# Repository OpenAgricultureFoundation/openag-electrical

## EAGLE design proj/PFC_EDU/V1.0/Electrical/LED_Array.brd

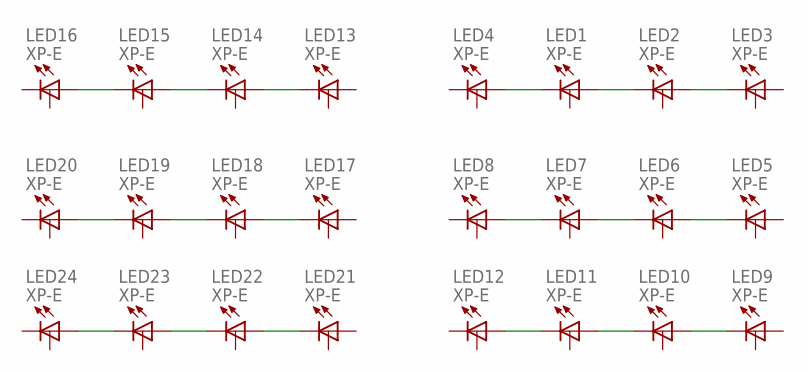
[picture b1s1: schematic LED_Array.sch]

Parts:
LED1, LED2, LED3, LED4, LED5, LED6, LED7, LED8, LED9, LED10, LED11, LED12, LED13, LED14, LED15, LED16, LED17, LED18, LED19, LED20, LED21, LED22, LED23, LED24: XP-E; CREE-XLAMP-XP-E

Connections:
unnamed: LED1.C, LED1.C@1 (C), LED4.A, LED4.A@1 (A)
unnamed: LED1.A, LED1.A@1 (A), LED2.C, LED2.C@1 (C)
unnamed: LED2.A, LED2.A@1 (A), LED3.C, LED3.C@1 (C)
unnamed: LED7.C, LED7.C@1 (C), LED8.A, LED8.A@1 (A)
unnamed: LED6.C, LED6.C@1 (C), LED7.A, LED7.A@1 (A)
unnamed: LED5.C, LED5.C@1 (C), LED6.A, LED6.A@1 (A)
unnamed: LED11.C, LED11.C@1 (C), LED12.A, LED12.A@1 (A)
unnamed: LED10.C, LED10.C@1 (C), LED11.A, LED11.A@1 (A)
unnamed: LED9.C, LED9.C@1 (C), LED10.A, LED10.A@1 (A)
unnamed: LED15.C, LED15.C@1 (C), LED16.A, LED16.A@1 (A)
unnamed: LED14.C, LED14.C@1 (C), LED15.A, LED15.A@1 (A)
unnamed: LED13.C, LED13.C@1 (C), LED14.A, LED14.A@1 (A)
unnamed: LED19.C, LED19.C@1 (C), LED20.A, LED20.A@1 (A)
unnamed: LED18.C, LED18.C@1 (C), LED19.A, LED19.A@1 (A)
unnamed: LED17.C, LED17.C@1 (C), LED18.A, LED18.A@1 (A)
unnamed: LED23.C, LED23.C@1 (C), LED24.A, LED24.A@1 (A)
unnamed: LED22.C, LED22.C@1 (C), LED23.A, LED23.A@1 (A)
unnamed: LED21.C, LED21.C@1 (C), LED22.A, LED22.A@1 (A)

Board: 2 copper layers, 24 parts (0 on the bottom side), 18 nets, no tracks yet.

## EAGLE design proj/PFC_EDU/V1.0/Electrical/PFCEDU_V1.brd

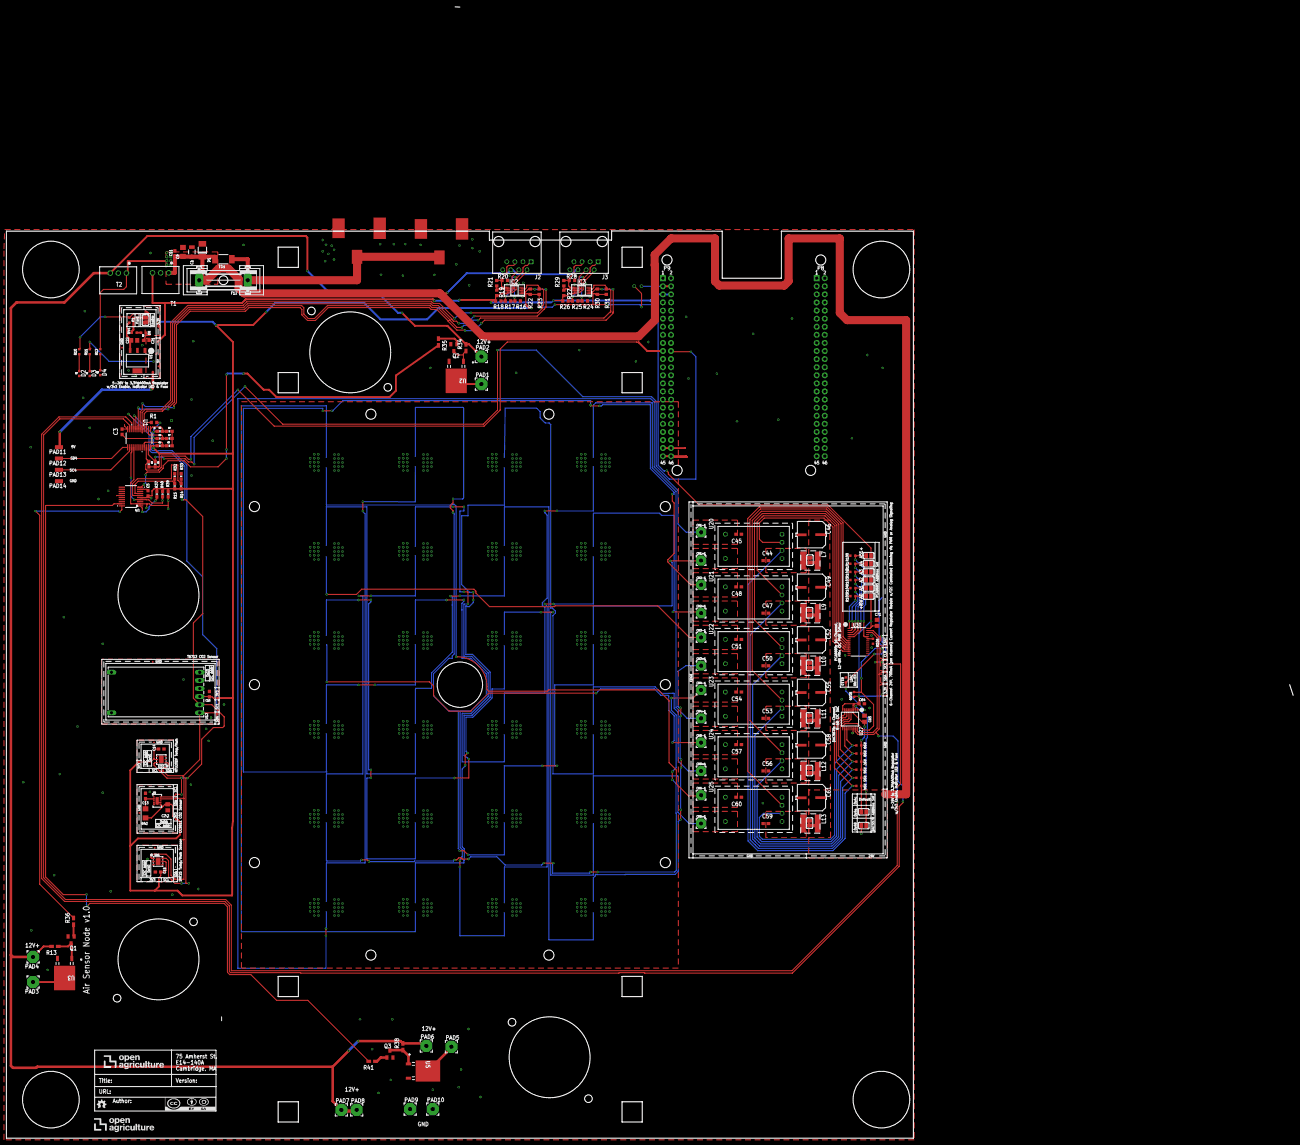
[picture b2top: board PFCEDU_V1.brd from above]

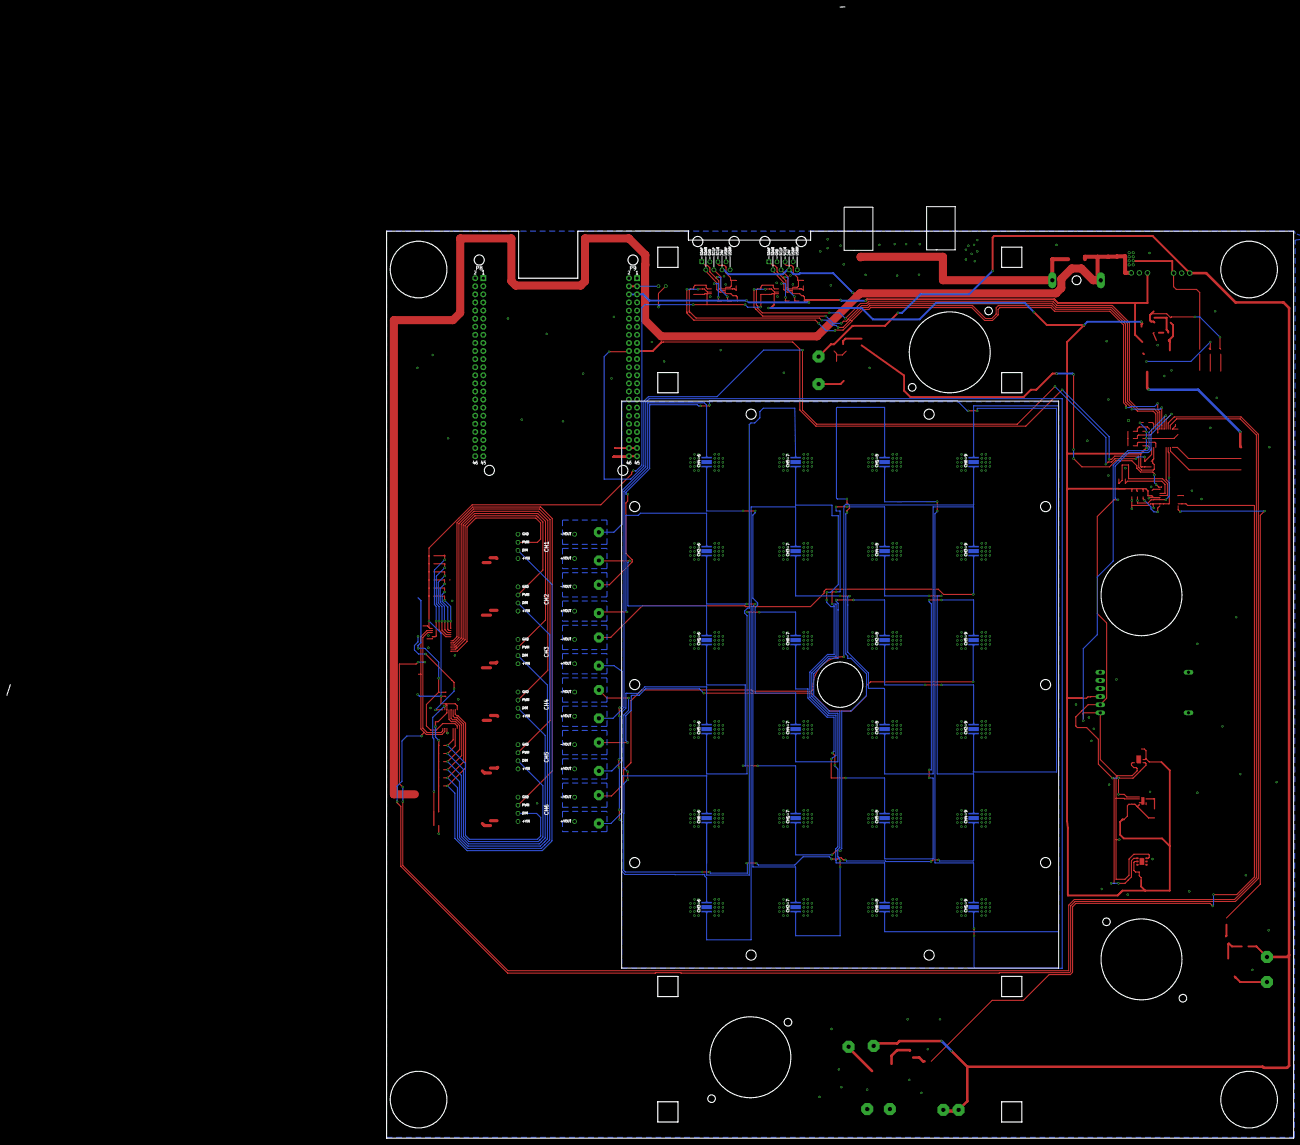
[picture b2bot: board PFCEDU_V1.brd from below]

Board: 2 copper layers, 284.7 x 284.8 mm, 221 parts (24 on the bottom side), 114 nets.

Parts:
ATTRIBUTES: DOCFIELD
C1: 4.7uF; CAP_C1206
C2\2, C65: 4.7uF; C0805
C3, C5, C11: .1uF; C0603@1
C9: 10uF; C1206
C13, C14, C15, C16, C21, C64: 0.1uF; C0603
C22, C71: 10uF; C0805
C44, C45, C47, C48, C50, C51, C53, C54, C56, C57, C59, C60: 10nF; C0603
C46, C49, C52, C55, C58, C61: 100uF; EEE-1HA101UP
CH1+1, CH1-1, CH2+1, CH2-1, CH3+1, CH3-1, CH4+1, CH4-1, CH5+1, CH5-1, CH6+1, CH6-1: 3,17/1,3
CH1-6, CH1-7, CH1-8, CH1-9, CH2-6, CH2-7, CH2-8, CH2-9, CH3-6, CH3-7, CH3-8, CH3-9, CH4-6, CH4-7, CH4-8, CH4-9, CH5-6, CH5-7, CH5-8, CH5-9, CH6-6, CH6-7, CH6-8, CH6-9: XP-E; CREE-XLAMP-XP-E
D1: SMAJ14A; DO-214AC
D2, D3, D4, D8: APT1608CGCK; CHIPLED_0603
F1: 0448.400MR; 0603
F11: SST 7; SS
F12: GSH15
IC2, IC3: PCA9615DP; SOP50P490X110-10N
J2, J3: 54602-908LF; OPENAG-V1-RJ45
L7, L9, L10, L11, L12, L13: 120uH; 74404064121
PAD1, PAD2, PAD3, PAD4, PAD5, PAD6, PAD7, PAD8, PAD9, PAD10: WIREPAD3,81/1,3; 3,81/1,3
PAD11, PAD12, PAD13, PAD14: SMD1,27-2,54
Q1, Q2, Q3: MMBT2222A; SOT23-BEC
R1, R22, R23, R30, R31: 10K; R0603
R2, R3, R4, R5, R6, R7, R8, R9, R14, R15, R32, R33, R37, R39, R40: 10K; 0603-RES
R10, R11, R12, R44: 100; RC0603N
R13, R34, R35, R36, R38, R41: R0805W
R16, R18, R19, R20, R24, R26, R27, R28: 600; R0603
R17, R21, R25, R29: 120; R0603
R42: 4.7K; R1206
R94, R95, R96, R97, R98, R99, R109: 1K; RC0603N
R100, R101, R102, R103, R104, R105, R106: 10K; RC0603N
R110: 0 OHM; RC0603N
SJ1: SOLDERJUMPER_REFLOW_NOPASTE
SJ_A18, SJ_A19, SJ_A20, SJ_A21, SJ_A22, SJ_A23, SJ_A24, SJ_A25, SJ_A26, SJ_A27, SJ_A28, SJ_A29, SJ_A34, SJ_A35: SOLDERJUMPER_REFLOW_NOPASTE
T1: R-78E5.0-1.0
T2: R-78E12.0-1.0; R-78E5.0-1.0
TP1, TP2, TP3, TP5, TP6, TP7, TP36, TP37, TP38, TP39, TP40, TP41, TP42, TP43, TP44, TP45, TP61, TP62, TP63: TPTP06R; TP06R
U1: TCA9548APWRPW24-M; PW24-M
U2, U3, U5: STD12NF06LT4; DPAK
U4: PCF8574APWRPW20-M; PW20-M
U9: CCS811
U10: HPP845E034R5; HTU20D(F)
U11: SHT25; SHT2X
U12: T6713-5K; T6713
U17: LM2937IMP3.3NOPB; MP04A
U20, U21, U22, U23, U24, U25: RCD-24-0.70/VREF; RCD-24-PINNED
U27: DAC5578SPW; TSSOP16
U30: PCA9685; TSSOP28
U$1, U$3: PJ-036AH
U$2: BEAGLE_BONE_BLACK_CAPE
U$9: OPENAG-LOGO-750-MIL

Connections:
24V_IN: F11.1, F12.1, U$1.1, U$3.1
!LDAC!: R110.2, U27.1
+3V3: C2\2.1, C3.1, C5.1, C14.1, C15.1, C16.1, C64.1, C65.1, C71.1, F1.2, IC2.1, IC3.1, R1.2, R2.2, R4.2, R6.2, R8.2, R9.2, R10.2, R14.2, R15.2, R22.2, R23.2, R30.2, R31.2, R37.2, R39.2, R40.2, R42.2, R94.1, R95.1, R96.1, R97.1, R98.1, R99.1, R109.1, SJ1.2, SJ_A18.1, SJ_A19.1, SJ_A20.1, SJ_A21.1, SJ_A22.1, SJ_A23.1, SJ_A34.1, TP5.TP, TP36.TP, TP41.TP, TP44.TP, TP63.TP, U1.24, U4.5, U9.6, U10.5, U11.5, U12.3, U27.3, U27.8, U30.28, U$2.P9.3, U$2.P9.4
+5V: C21.1, IC2.10, IC3.10, PAD11.1, R11.2, R18.1, R19.2, R26.1, R27.2, T1.3, TP62.TP, U17.1, U$2.P9.5, U$2.P9.6
+12V: PAD2.1, PAD4.1, PAD6.1, PAD7.1, PAD8.1, R13.2, R34.2, R38.2, T2.3
+24V: C1.1, C9.1, C11.1, C46.+, C49.+, C52.+, C55.+, C58.+, C61.+, D1.C, F11.2, F12.2, J2.24V(6), J3.24V(6), L7.1, L9.1, L10.1, L11.1, L12.1, L13.1, R12.2, SJ_A24.2, SJ_A25.2, SJ_A26.2, SJ_A27.2, SJ_A28.2, SJ_A29.2, T1.1, T2.1
A0: R105.2, SJ_A18.2, U30.1
A0_EXT_1: R4.1, R5.2, U1.1
A0_IO: R14.1, R33.2, U4.6
A1: R104.2, SJ_A19.2, U30.2
A1_EXT_1: R6.1, R7.2, U1.2
A1_IO: R15.1, R32.2, U4.7
A2: R103.2, SJ_A20.2, U30.3
A2_EXT_1: R2.1, R3.2, U1.21
A3: R102.2, SJ_A21.2, U30.4
A4: R101.2, SJ_A22.2, U30.5
A5: R100.2, SJ_A23.2, U30.24
ADDR0: SJ_A34.2, SJ_A35.2, U27.2
CH1+: CH1+1.1, CH1-6.A, CH1-6.A@1, U20.6
CH1-: C45.1, CH1-1.1, CH1-9.C, CH1-9.C@1, U20.5
CH2+: CH2+1.1, CH2-6.A, CH2-6.A@1, U21.6
CH2-: C48.1, CH2-1.1, CH2-9.C, CH2-9.C@1, U21.5
CH3+: CH3+1.1, CH3-6.A, CH3-6.A@1, U22.6
CH3-: C51.1, CH3-1.1, CH3-9.C, CH3-9.C@1, U22.5
CH4+: CH4+1.1, CH4-6.A, CH4-6.A@1, U23.6
CH4-: C54.1, CH4-1.1, CH4-9.C, CH4-9.C@1, U23.5
CH5+: CH5+1.1, CH5-6.A, CH5-6.A@1, U24.6
CH5-: C57.1, CH5-1.1, CH5-9.C, CH5-9.C@1, U24.5
CH6+: CH6+1.1, CH6-6.A, CH6-6.A@1, U25.6
CH6-: C60.1, CH6-1.1, CH6-9.C, CH6-9.C@1, U25.5
DAC_!CLR!: R109.2, U27.9
DIM1: R94.2, U20.2, U27.7
DIM2: R95.2, U21.2, U27.6
DIM3: R96.2, U22.2, U27.5
DIM4: R97.2, U23.2, U27.4
DIM5: R98.2, U24.2, U27.10
DIM6: R99.2, U25.2, U27.11
DSCLM0: IC2.6, J2.DSCLM(5), R20.2, R21.1
DSCLM1: IC3.6, J3.DSCLM(5), R28.2, R29.1
DSCLP0: IC2.7, J2.DSCLP(4), R19.1, R21.2
DSCLP1: IC3.7, J3.DSCLP(4), R27.1, R29.2
DSDAM0: IC2.9, J2.DSDAM(2), R16.1, R17.2
DSDAM1: IC3.9, J3.DSDAM(2), R24.1, R25.2
DSDAP0: IC2.8, J2.DSDAP(1), R17.1, R18.2
DSDAP1: IC3.8, J3.DSDAP(1), R25.1, R26.2
GND: C1.2, C2\2.2, C3.2, C5.2, C9.2, C11.2, C13.2, C14.2, C15.2, C16.2, C21.2, C22.2, C44.2, C45.2, C46.-, C47.2, C48.2, C49.-, C50.2, C51.2, C52.-, C53.2, C54.2, C55.-, C56.2, C57.2, C58.-, C59.2, C60.2, C61.-, C64.2, C65.2, C71.2, D1.A, D2.C, D3.C, D4.C, D8.C, IC2.5, IC3.5, J2.GND(3), J3.GND(3), PAD9.1, PAD10.1, PAD14.1, Q1.E, Q2.E, Q3.E, R3.1, R5.1, R7.1, R16.2, R20.1, R24.2, R28.1, R32.1, R33.1, R100.1, R101.1, R102.1, R103.1, R104.1, R105.1, R106.2, R110.1, SJ_A35.1, T1.2, T2.2, TP3.TP, TP37.TP, TP40.TP, TP45.TP, TP61.TP, U1.12, U2.2, U3.2, U4.9, U4.15, U5.2, U9.1, U9.7, U9.EP, U10.2, U11.2, U12.4, U12.6, U17.2, U17.4, U20.4, U21.4, U22.4, U23.4, U24.4, U25.4, U27.14, U30.14, U30.25, U$1.2, U$1.3, U$2.P8.1, U$2.P8.2, U$2.P9.1, U$2.P9.2, U$2.P9.43, U$2.P9.44, U$2.P9.45, U$2.P9.46, U$3.2, U$3.3
MOS1: PAD3.1, U3.3
MOS2: PAD1.1, U2.3
MOS3: PAD5.1, U5.3
unnamed: D3.A, R11.1
unnamed: D4.A, R12.1
unnamed: Q1.C, R13.1, U3.1
unnamed: Q1.B, R36.1
unnamed: D2.A, R10.1
unnamed: R37.1, U4.1
unnamed: Q2.C, R34.1, U2.1
unnamed: Q2.B, R35.1
unnamed: Q3.C, R38.1, U5.1
unnamed: Q3.B, R41.1
unnamed: CH2-8.C, CH2-8.C@1, CH2-9.A, CH2-9.A@1
unnamed: CH2-7.C, CH2-7.C@1, CH2-8.A, CH2-8.A@1
unnamed: CH2-6.C, CH2-6.C@1, CH2-7.A, CH2-7.A@1
unnamed: CH4-8.C, CH4-8.C@1, CH4-9.A, CH4-9.A@1
unnamed: CH4-7.C, CH4-7.C@1, CH4-8.A, CH4-8.A@1
unnamed: CH4-6.C, CH4-6.C@1, CH4-7.A, CH4-7.A@1
unnamed: CH6-8.C, CH6-8.C@1, CH6-9.A, CH6-9.A@1
unnamed: CH6-7.C, CH6-7.C@1, CH6-8.A, CH6-8.A@1
unnamed: C44.1, L7.2, SJ_A24.1, U20.1
unnamed: C47.1, L9.2, SJ_A25.1, U21.1
unnamed: C50.1, L10.2, SJ_A26.1, U22.1
unnamed: C53.1, L11.2, SJ_A27.1, U23.1
unnamed: U9.4, U9.5
unnamed: C13.1, R42.1, U9.2
unnamed: C56.1, L12.2, SJ_A28.1, U24.1
unnamed: C59.1, L13.2, SJ_A29.1, U25.1
unnamed: CH6-6.C, CH6-6.C@1, CH6-7.A, CH6-7.A@1
unnamed: CH1-8.C, CH1-8.C@1, CH1-9.A, CH1-9.A@1
unnamed: CH1-7.C, CH1-7.C@1, CH1-8.A, CH1-8.A@1
unnamed: CH1-6.C, CH1-6.C@1, CH1-7.A, CH1-7.A@1
unnamed: CH3-8.C, CH3-8.C@1, CH3-9.A, CH3-9.A@1
unnamed: CH3-7.C, CH3-7.C@1, CH3-8.A, CH3-8.A@1
unnamed: CH3-6.C, CH3-6.C@1, CH3-7.A, CH3-7.A@1
unnamed: CH5-8.C, CH5-8.C@1, CH5-9.A, CH5-9.A@1
unnamed: CH5-7.C, CH5-7.C@1, CH5-8.A, CH5-8.A@1
unnamed: CH5-6.C, CH5-6.C@1, CH5-7.A, CH5-7.A@1
unnamed: D8.A, R44.1
unnamed: C22.1, F1.1, U17.3
OE: R106.1, U30.23
P0_IO: R35.2, U4.10
P6_IO: R41.2, U4.19
P7_IO: R36.2, U4.20
PWM1: U20.3, U30.12
PWM2: U21.3, U30.11
PWM3: U22.3, U30.10
PWM4: U23.3, U30.9
PWM5: U24.3, U30.8
PWM6: U25.3, U30.7
REG_3V3_400MA: R44.2, SJ1.1
RESET1: R1.1, U1.3
SC0: IC2.4, R23.1, U1.5
SC1: IC3.4, R31.1, U1.7
SC2: TP1.TP, TP7.TP, TP39.TP, TP43.TP, U1.9, U9.10, U10.6, U11.6, U12.2
SC3: U1.11, U27.16, U30.26
SC4: PAD13.1, U1.14
SC5: R39.1, U1.16, U4.2
SCL: R8.1, U1.22, U$2.P9.19
SD0: IC2.2, R22.1, U1.4
SD1: IC3.2, R30.1, U1.6
SD2: TP2.TP, TP6.TP, TP38.TP, TP42.TP, U1.8, U9.9, U10.1, U11.1, U12.1
SD3: U1.10, U27.15, U30.27
SD4: PAD12.1, U1.13
SD5: R40.1, U1.15, U4.4
SDA: R9.1, U1.23, U$2.P9.20
T1: CH1-6.THERM, CH1-7.THERM, CH1-8.THERM, CH1-9.THERM, CH2-6.THERM, CH2-7.THERM, CH2-8.THERM, CH2-9.THERM, CH3-6.THERM, CH3-7.THERM, CH3-8.THERM, CH3-9.THERM, CH4-6.THERM, CH4-7.THERM, CH4-8.THERM, CH4-9.THERM, CH5-6.THERM, CH5-7.THERM, CH5-8.THERM, CH5-9.THERM, CH6-6.THERM, CH6-7.THERM, CH6-8.THERM, CH6-9.THERM

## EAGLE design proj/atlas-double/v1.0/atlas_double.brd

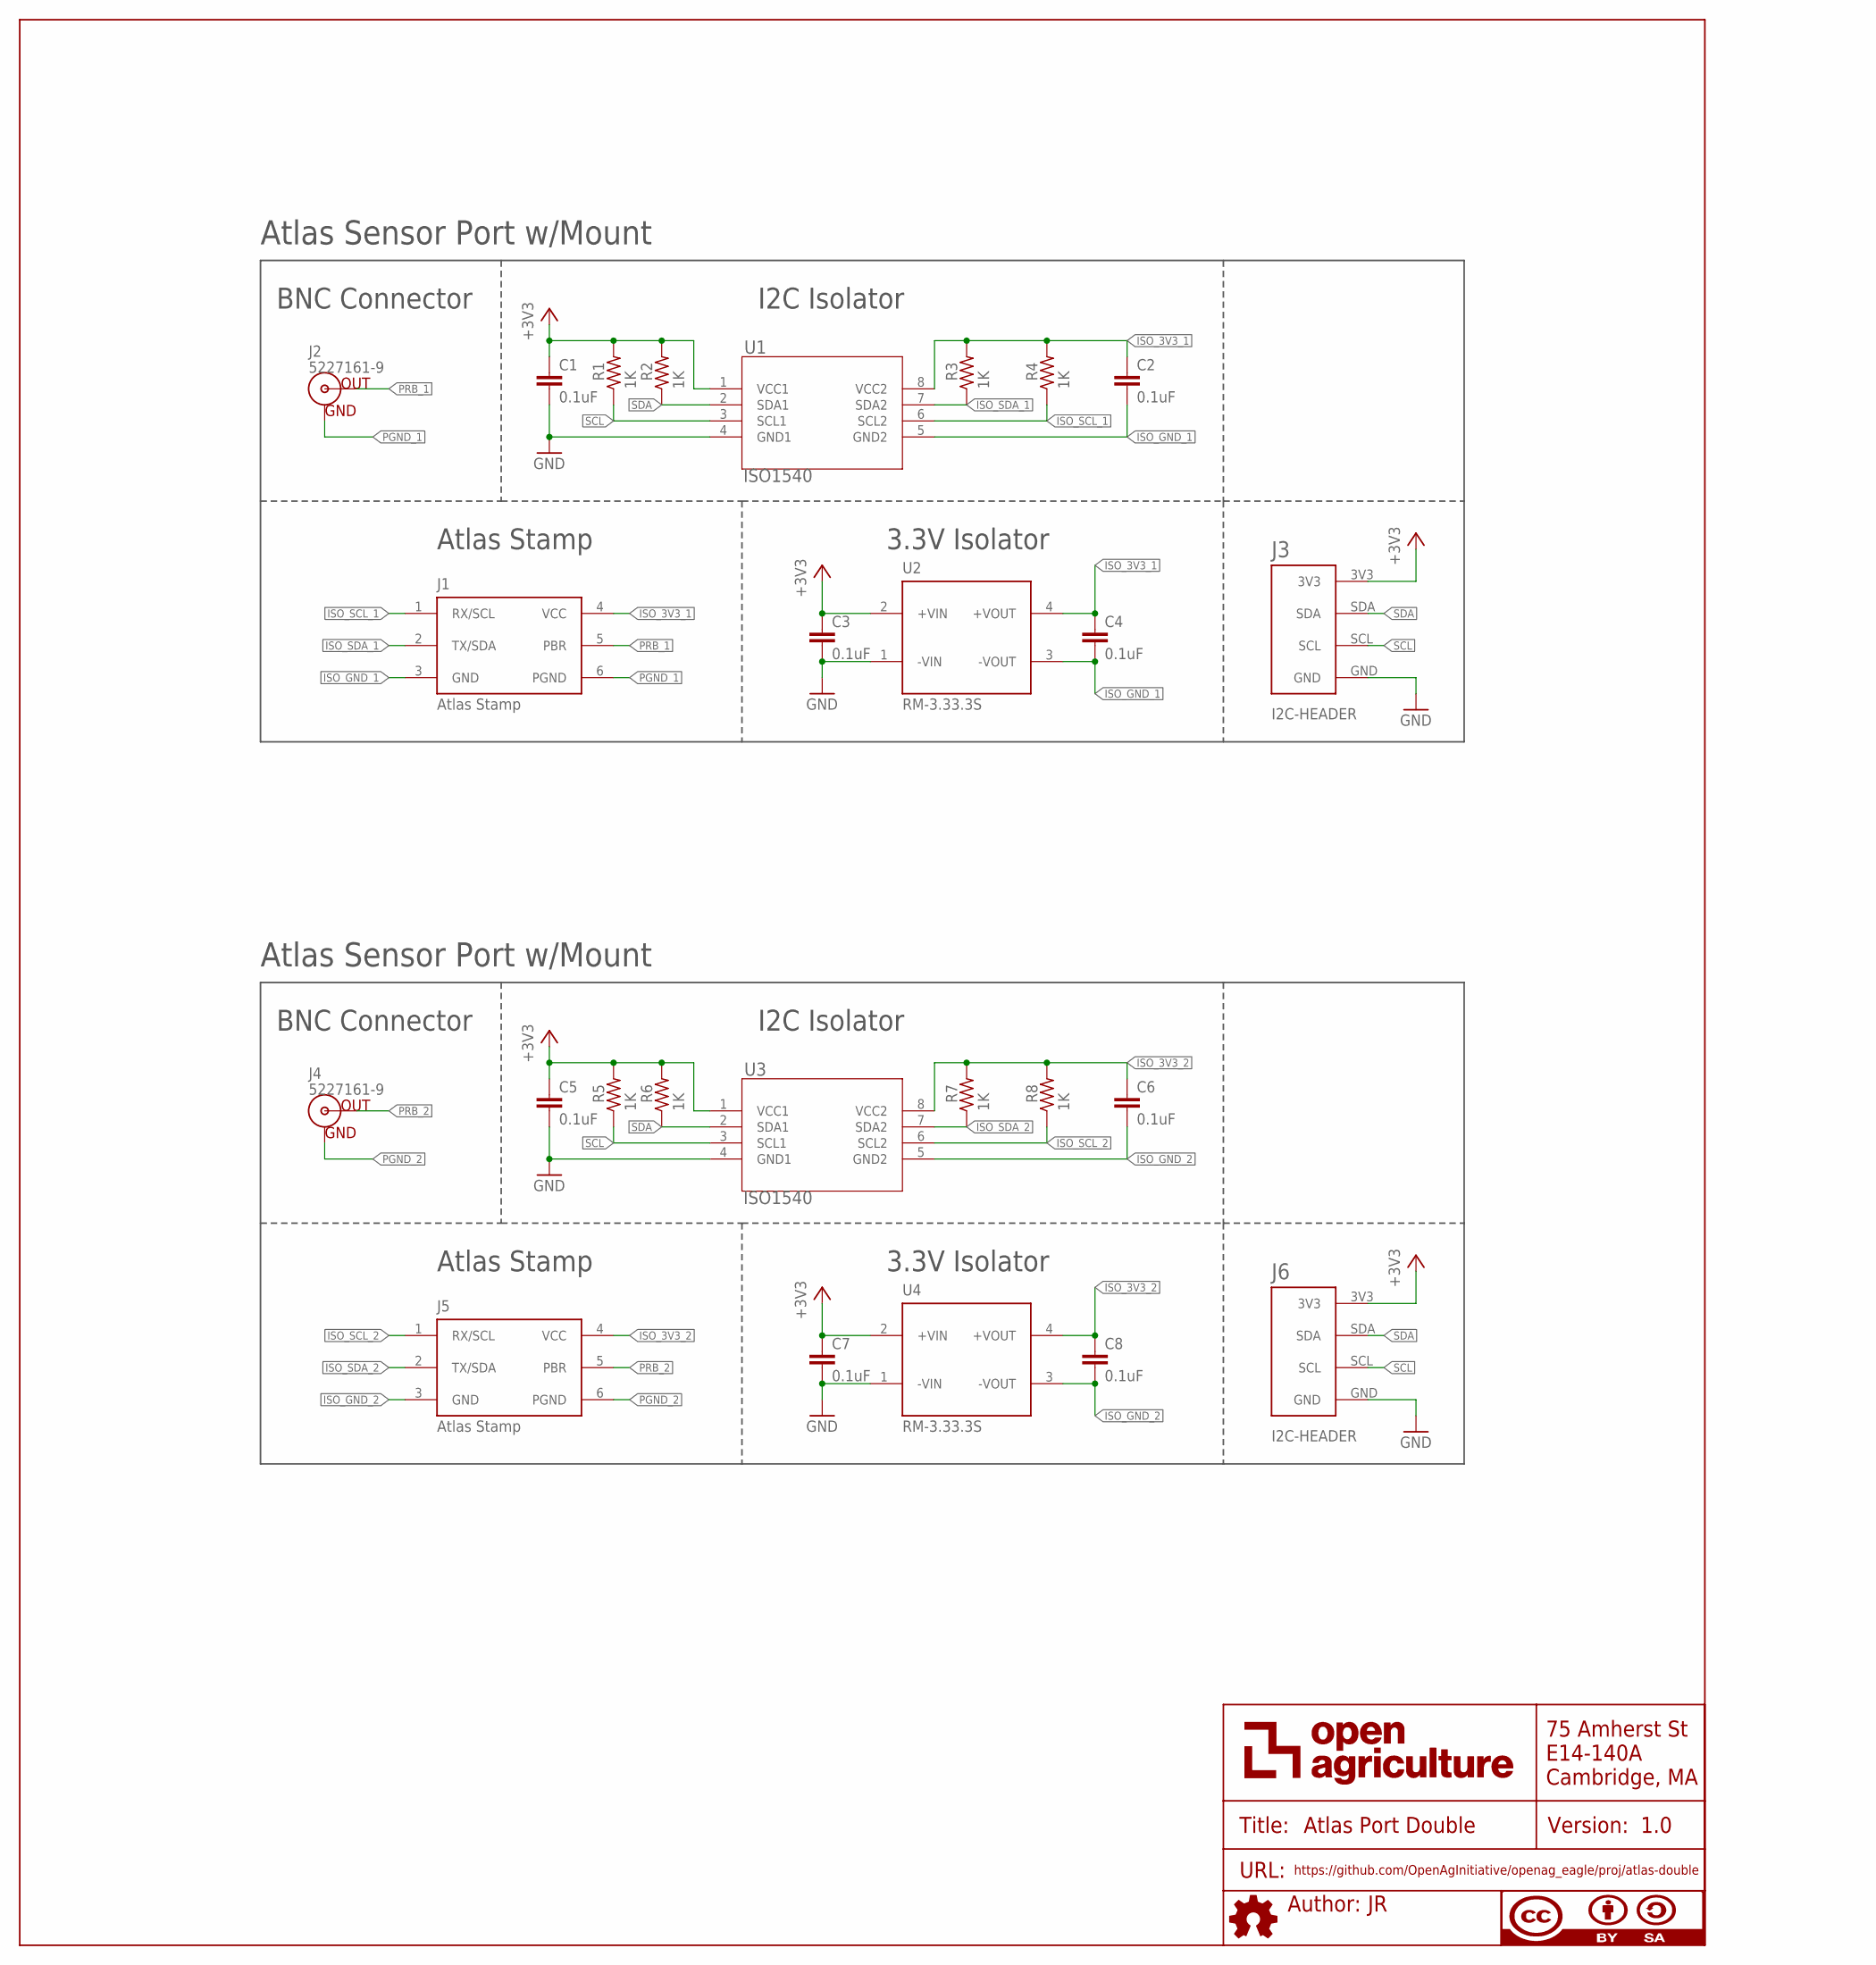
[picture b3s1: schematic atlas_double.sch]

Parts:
C1, C2, C3, C4, C5, C6, C7, C8: 0.1uF; C0603
FRAME1: DOCFIELD
J1, J5: Atlas Stamp; ATLAS-STAMP
J2, J4: 5227161-9; BNC
J3, J6: I2C-HEADER; OPENAG-I2C-HEADER
R1, R2, R3, R4, R5, R6, R7, R8: 1K; RC0603N
U1, U3: ISO1540; D8
U2, U4: RM-3.33.3S; SIP4

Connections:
+3V3: C1.1, C3.1, C5.1, C7.1, J3.3V3, J6.3V3, R1.2, R2.2, R5.2, R6.2, U1.1 (VCC1), U2.2 (+VIN), U3.1 (VCC1), U4.2 (+VIN)
GND: C1.2, C3.2, C5.2, C7.2, J3.GND, J6.GND, U1.4 (GND1), U2.1 (-VIN), U3.4 (GND1), U4.1 (-VIN)
ISO_3V3_1: C2.1, C4.1, J1.4 (VCC), R3.2, R4.2, U1.8 (VCC2), U2.4 (+VOUT)
ISO_3V3_2: C6.1, C8.1, J5.4 (VCC), R7.2, R8.2, U3.8 (VCC2), U4.4 (+VOUT)
ISO_GND_1: C2.2, C4.2, J1.3 (GND), U1.5 (GND2), U2.3 (-VOUT)
ISO_GND_2: C6.2, C8.2, J5.3 (GND), U3.5 (GND2), U4.3 (-VOUT)
ISO_SCL_1: J1.1 (RX/SCL), R4.1, U1.6 (SCL2)
ISO_SCL_2: J5.1 (RX/SCL), R8.1, U3.6 (SCL2)
ISO_SDA_1: J1.2 (TX/SDA), R3.1, U1.7 (SDA2)
ISO_SDA_2: J5.2 (TX/SDA), R7.1, U3.7 (SDA2)
PGND_1: J1.6 (PGND), J2.GND
PGND_2: J4.GND, J5.6 (PGND)
PRB_1: J1.5 (PBR), J2.S (OUT)
PRB_2: J4.S (OUT), J5.5 (PBR)
SCL: J3.SCL, J6.SCL, R1.1, R5.1, U1.3 (SCL1), U3.3 (SCL1)
SDA: J3.SDA, J6.SDA, R2.1, R6.1, U1.2 (SDA1), U3.2 (SDA1)

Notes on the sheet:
3.3V Isolator
I2C Isolator
Atlas Stamp
BNC Connector
Atlas Sensor Port w/Mount

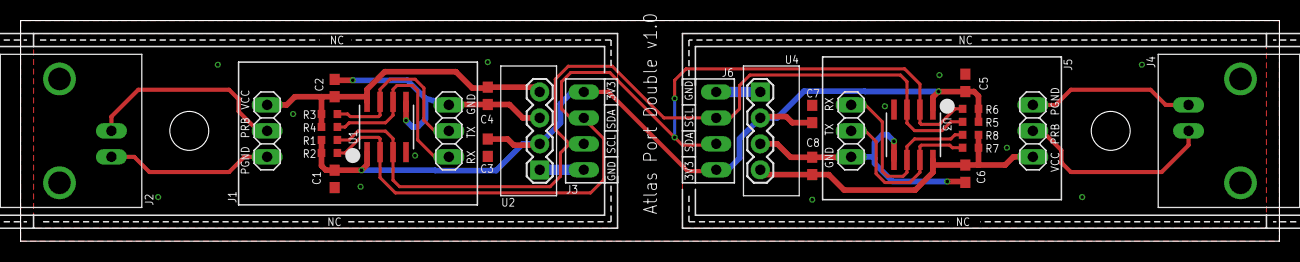
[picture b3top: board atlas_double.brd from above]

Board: 2 copper layers, 123.2 x 21.6 mm, 30 parts (1 on the bottom side), 16 nets.

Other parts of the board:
U$2, U$3: OPENAG-CORNER-MOUNTING-HOLE
U$5: OPENAG-LOGO-750-MIL

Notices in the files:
parts and their libraries:
SparkFun-Resistors: Licensing: Creative Commons ShareAlike 4.0 International - https://creativecommons.org/licenses/by-sa/4.0
SparkFun-Boards: Licensing: CC v3.0 Share-Alike You are welcome to use this library for commercial purposes.
